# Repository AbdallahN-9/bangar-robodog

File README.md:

# Bangar Robodog (بنجر) 🐕⚙️

### An Assistive Wheeled-Quadruped Robot Dog: Custom Embedded Hardware, ROS 2 & Gazebo Simulation

**Bangar** is an award-winning, custom-engineered **wheeled-quadruped robot dog** developed as an assistive, domestic companion robot. Designed to alleviate elderly loneliness and offer non-intrusive health/emergency monitoring, Bangar integrates custom embedded electronics, 12-DoF hybrid locomotion, and high-fidelity physics simulation in ROS 2 and Gazebo Sim.

---

## 👥 The Team & IEEE Recognition

Project Bangar was engineered by:

* **Abdallah Nabil** — *Electrical System & Gazebo Simulation*
* **Omar Khaled** — *Mechanical Design & Control Software*
* **Omar Barakat** — *Mechanical Assembly & Computer Vision*
* **Khaled Aboelmaety** — *Sensor Integration & System Debugging*

| IEEE ICMISI 2026 Exhibition & Award | IEEE Certificate of Recognition |
| :---: | :---: |
|  |  |
| The team showcasing Bangar at the 2026 IEEE 3rd International Conference on Machine Intelligence and Smart Innovation (ICMISI 2026). | **Official Recognition**: Presented by IEEE and the Arab Academy for Science, Technology & Maritime Transport (AASTMT). |

<p align="center">
  
  <br />
  <em>Concept: Bangar as an assistive companion in home living environments.</em>
</p>

---

## 🛠️ Custom Hardware, PCB & Wiring Integration

Bangar is powered by a custom-designed, multi-layer motherboard developed in **KiCad** ($107.25\text{ mm} \times 92.0\text{ mm}$) to handle power regulation, high-torque servo actuation, and distributed sensor processing:

| Fabricated Motherboard | KiCad 3D Component Layout |
| :---: | :---: |
|  |  |
| **Physical PCB:** Dual microcontroller sockets, screw power rails, blade fuse, and JST headers. | **3D CAD Layout:** Component placement, PCA9685 PWM headers, and terminal connectors. |

| Workbench Wiring & Sensor Testing | Full In-Chassis Electrical Integration |
| :---: | :---: |
|  |  |
| **Bench Testing:** Full testbench wiring with ultrasonic sensor arrays and dual Nano logic. | **Chassis Integration:** LiPo battery pack, buck converters, motherboard, and servo cabling. |

### Motherboard Architecture & Electronics Specifications

* **Processing & Logic:** Dual **Arduino Nano v3.x** microcontrollers for distributed motor control, kinematics timing, and sensor telemetry.
* **Actuator Control:** Dedicated 16-channel **PCA9685** 12-bit PWM servo controller interface (`PCA_In`) driving the 8 shoulder and knee servo motors (`J1`–`J8`, `J18`–`J21`).
* **Multi-Rail Power System:**
  * **12V High-Power Input/Output:** Screw terminal distribution for wheel drive motors and main battery input.
  * **6V High-Current Rail:** Dedicated high-amperage power distribution specifically tuned for the 8 high-torque leg servos.
  * **5V Logic Rail:** Regulated supply for microcontrollers, sensors, and logic lines.
  * **Circuit Protection:** Built-in automotive blade fuse holder and heavy-duty primary power toggle switch.
* **Sensors & Expansion Interfaces:**
  * Multi-channel **Ultrasonic Range Sensors** (`UltraS1`, `UltraS2`, etc.) via polarized JST connectors.
  * **Hall-Effect Wheel Encoders** (`Hall_Effect2`, `Hall_Effect3`) for wheel odometry and speed feedback.
  * **I2C Telemetry Bus:** Exposed SDA, SCL, 5V, GND, and INT breakout for IMU and expansion peripherals.
* **Fabrication Files:** Complete Gerber archives (`hardware/gerber/bangar_107.25x92.0mm_gerber.zip`) ready for direct manufacturing (JLCPCB, PCBWay, etc.).

---

## 📸 Simulation & Kinematics Showcase

| Gazebo Sim Warehouse Environment | RViz2 Kinematics & TF Model |
| :---: | :---: |
|  |  |
| **Gazebo Sim:** ODE physics, custom friction zones ($\mu=0.2$ to $\mu=50$), and navigation arenas. | **RViz2:** Joint coordinate frames, link geometry, acrylic chassis, and top phone mount. |

<p align="center">
  
  <br />
  <em>CAD render showcasing mechanical leg linkages, wheel assemblies, chassis cutouts, and smartphone mount.</em>
</p>

---

## 🌟 Key Locomotion & Software Features

- **Hybrid Legged-Wheeled Locomotion:**
  - **Quadruped Trot Gait:** Diagonal pair trotting (FL+BR in phase, FR+BL in antiphase) with coordinated shoulder sweeps and knee clearance arches.
  - **Differential Wheeled Drive:** 4 powered wheels (Pololu 60×8mm) located at the feet enable zero-radius in-place turns and fast flat-ground translation.
  - **Smooth Eased Poses:** Sitting, standing, and stopping postures generated via cosine easing interpolation.
- **Gazebo Sim Physics & Controllers:**
  - 8 Position PID controllers for shoulders ($P=150$) and knees ($P=40$).
  - 4 Velocity controllers for wheel driving ($P=10.0$).
  - Custom `warehouse_world.sdf` featuring a $30\text{m} \times 24\text{m}$ warehouse arena with colored navigation goals and a low-friction terrain zone ($\mu=0.2$) for traction testing.
- **Perception & Localization:**
  - Smartphone head bracket (`mobile_link`) with DroidCam IP stream integration.
  - Real-time ArUco fiducial marker tracking (`cv2.aruco`) for 2D world pose estimation.
  - ROS 2 message bridging for multi-directional ultrasonic proximity scanning.

---

## 📐 Kinematics & Joint Mapping

Bangar possesses **12 actuated Degrees of Freedom (DoF)**:

| Joint Group | Joints | Type | Limits / Range | Function |
| :--- | :--- | :--- | :--- | :--- |
| **Shoulders (4×)** | `front_left_shoulder_joint`<br>`front_right_shoulder_joint`<br>`back_left_shoulder_joint`<br>`back_right_shoulder_joint` | Revolute | $\pm 0.8\text{ rad}$ ($50\text{ N}\cdot\text{m}$) | Forward/rearward leg swing |
| **Knees (4×)** | `front_left_knee_joint`<br>`front_right_knee_joint`<br>`back_left_knee_joint`<br>`back_right_knee_joint` | Revolute | $\pm 1.2\text{ rad}$ / $\pm 1.4\text{ rad}$ | Leg lifting & ground clearance |
| **Wheels (4×)** | `front_left_wheel_joint`<br>`front_right_wheel_joint`<br>`back_left_wheel_joint`<br>`back_right_wheel_joint` | Continuous | Continuous ($10\text{ rad/s}$) | Driving & skid-steer turning |

---

## 📂 Repository Structure

```
bangar/
├── CMakeLists.txt              # Package build definitions & install targets
├── package.xml                 # ROS 2 package metadata and dependencies
├── README.md                   # Comprehensive project documentation
├── .gitignore                  # Git exclusions for build & temporary files
├── hardware/                   # Custom embedded electronics design
│   ├── kicad/                  # KiCad PCB project, schematic & layout files
│   └── gerber/                 # Ready-to-order manufacturing Gerber packages
├── docs/
│   └── images/                 # Simulation screenshots, PCB photos, wiring & CAD renders
├── config/
│   └── joint_names_Bangar.yaml # Joint names configuration
├── launch/
│   ├── gazebo_launch.py        # Complete headless/macOS-safe Gazebo launch
│   ├── gazebo_walk.launch.py   # Gazebo simulation with walk controller
│   ├── display.launch.py       # Basic robot state display in RViz
│   └── rviz.launch.py          # Interactive RViz2 visualization
├── urdf/
│   ├── bangar.urdf             # Baseline URDF model
│   ├── bangar_gazebo.urdf      # Gazebo simulation model with plugins & PIDs
│   └── bangar.csv              # Link masses, origins, and inertias
├── worlds/
│   └── warehouse_world.sdf     # Custom warehouse simulation arena
├── meshes/                     # STL geometry files for robot links & wheels
└── bangar/                     # ROS 2 Python nodes
    ├── __init__.py
    ├── bangar_controller.py    # Master state machine controller
    ├── walk_node.py            # Diagonal trot gait generator
    ├── wheel_node.py           # Wheel velocity publisher
    ├── sit_node.py             # Cosine-interpolated sitting motion
    ├── turn_left_node.py       # Differential skid turn (left)
    ├── turn_right_node.py      # Differential skid turn (right)
    └── camera_node.py          # ArUco marker pose estimator via camera feed
```

---

## 🚀 Getting Started

### 1. Prerequisites

- **OS:** Linux (Ubuntu 22.04 / 24.04) or macOS (Apple Silicon / Intel via Conda/RoboStack)
- **ROS 2:** Jazzy Jalisco or Humble Hawksbill
- **Gazebo Sim:** Gazebo Harmonic or Fortress (`gz-sim8`)
- **ROS-Gazebo Bridge:** `ros_gz_bridge`, `ros_gz_sim`
- **KiCad (Optional):** KiCad v7 or v8 (to view/edit PCB schematics)
- **Python Dependencies:** `opencv-python`, `numpy`, `cv_bridge`

### 2. Workspace Setup & Build

Clone into your ROS 2 workspace's `src` folder:

```bash
# Create and navigate to your ROS 2 workspace
mkdir -p ~/ros2_ws/src
cd ~/ros2_ws/src

# Clone the repository
git clone https://github.com/AbdallahN-9/bangar-robodog.git bangar

# Install ROS dependencies
cd ~/ros2_ws
rosdep install --from-paths src --ignore-src -r -y

# Build with colcon
colcon build --symlink-install

# Source the overlay
source install/setup.bash
```

*(On macOS using zsh, use `source install/setup.zsh`)*

---

## 🕹️ Running the Simulation

### Option A: Launch Full Gazebo Simulation

To launch the physics server, robot spawn, topic bridges, and behavioral controller:

```bash
ros2 launch bangar gazebo_launch.py
```

*Note for macOS users:* Gazebo server runs headless (`-s`) by default for optimal performance and stability.

### Option B: Interactive State & Motion Control

Command Bangar's locomotion modes on the `/bangar/mode` topic:

```bash
# Start walking (diagonal trot gait + wheel drive)
ros2 topic pub --once /bangar/mode std_msgs/msg/String "{data: 'walk'}"

# Turn left in place (differential wheel drive)
ros2 topic pub --once /bangar/mode std_msgs/msg/String "{data: 'turn_left'}"

# Turn right in place (differential wheel drive)
ros2 topic pub --once /bangar/mode std_msgs/msg/String "{data: 'turn_right'}"

# Sit down smoothly (cosine-interpolated rear leg fold)
ros2 topic pub --once /bangar/mode std_msgs/msg/String "{data: 'sit'}"

# Stand / Stop
ros2 topic pub --once /bangar/mode std_msgs/msg/String "{data: 'stop'}"
```

### Option C: View Kinematics in RViz2

To inspect the robot's URDF model and test gait movements visually without physics:

```bash
ros2 launch bangar rviz.launch.py
```

### Option D: Vision & Marker Tracking

To test ArUco marker pose localization from an IP phone camera feed:

```bash
ros2 run bangar camera_node.py
```

---

## 📡 Key Topics & Bridges

| Topic | Type | Source | Purpose |
| :--- | :--- | :--- | :--- |
| `/joint_states` | `sensor_msgs/msg/JointState` | Gazebo Sim | Current angles & velocities of all 12 joints |
| `/bangar/mode` | `std_msgs/msg/String` | User / Teleop | Mode selector (`walk`, `turn_left`, `sit`, `stop`) |
| `/cmd/*_shoulder` | `std_msgs/msg/Float64` | `bangar_controller` | Commanded shoulder joint target angle (rad) |
| `/cmd/*_knee` | `std_msgs/msg/Float64` | `bangar_controller` | Commanded knee joint target angle (rad) |
| `/cmd/*_wheel` | `std_msgs/msg/Float64` | `bangar_controller` | Commanded wheel joint angular velocity |
| `/bangar/pose_estimate` | `geometry_msgs/msg/PoseWithCovarianceStamped` | `camera_node` | Visual pose estimated from ArUco markers |

---

## 📄 License

This project is licensed under the [BSD-3-Clause License](LICENSE).

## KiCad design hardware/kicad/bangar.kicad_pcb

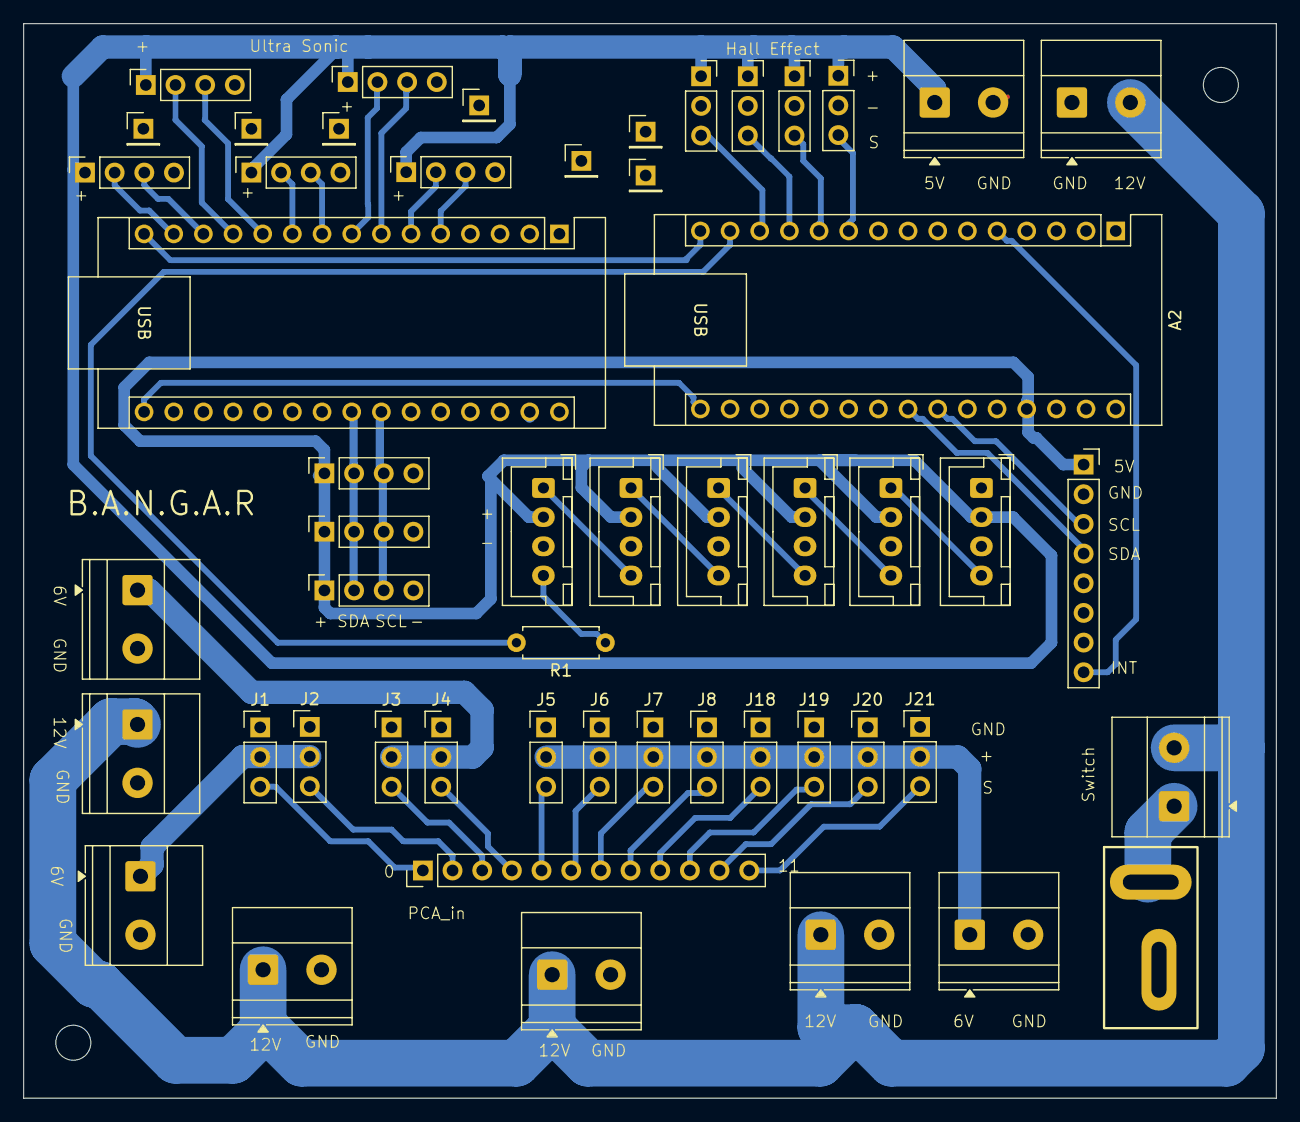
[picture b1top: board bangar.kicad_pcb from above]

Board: 2 copper layers, 107.2 x 92.0 mm, 53 parts (0 on the bottom side), 45 nets.

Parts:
A1, A2: Arduino_Nano_v3.x; Arduino_Nano
J1: Serv0; PinHeader_1x03_P2.54mm_Vertical
J2: Serv1; PinHeader_1x03_P2.54mm_Vertical
J3: Serv2; PinHeader_1x03_P2.54mm_Vertical
J4: Serv3; PinHeader_1x03_P2.54mm_Vertical
J5: Serv4; PinHeader_1x03_P2.54mm_Vertical
J6: Serv5; PinHeader_1x03_P2.54mm_Vertical
J7: Serv6; PinHeader_1x03_P2.54mm_Vertical
J8: Serv7; PinHeader_1x03_P2.54mm_Vertical
J9: UltraS1; PinSocket_1x04_P2.54mm_Vertical
J10: UltraS2; PinSocket_1x04_P2.54mm_Vertical
J11: UltraS3; PinSocket_1x04_P2.54mm_Vertical
J12: UltraS4; PinSocket_1x04_P2.54mm_Vertical
J14: 6V_Buck_2; TerminalBlock_Phoenix_MKDS-1,5-2_1x02_P5.00mm_Horizontal
J15: 6V_Buck_3; TerminalBlock_Phoenix_MKDS-1,5-2_1x02_P5.00mm_Horizontal
J16: 6V_Buck_4; TerminalBlock_Phoenix_MKDS-1,5-2_1x02_P5.00mm_Horizontal
J17: 5V_Buck; TerminalBlock_Phoenix_MKDS-1,5-2_1x02_P5.00mm_Horizontal
J18: Serv8; PinHeader_1x03_P2.54mm_Vertical
J19: Serv9; PinHeader_1x03_P2.54mm_Vertical
J20: Serv10; PinHeader_1x03_P2.54mm_Vertical
J21: Serv11; PinHeader_1x03_P2.54mm_Vertical
J22: PCA9685_in; PinHeader_1x12_P2.54mm_Vertical
J23: PCA; PinSocket_1x04_P2.54mm_Vertical
J24: Heart sensor; PinSocket_1x04_P2.54mm_Vertical
J25: mpu6050; PinSocket_1x08_P2.54mm_Vertical
J26: UltraS5; PinSocket_1x04_P2.54mm_Vertical
J27: Extra; PinSocket_1x04_P2.54mm_Vertical
J28: Hall_Effect1; PinSocket_1x03_P2.54mm_Vertical
J29: Hall_Effect2; PinSocket_1x03_P2.54mm_Vertical
J30: Hall_Effect3; PinSocket_1x03_P2.54mm_Vertical
J31: Hall_Effect4; PinSocket_1x03_P2.54mm_Vertical
J32: LED2; JST_XH_B4B-XH-A_1x04_P2.50mm_Vertical
J33: LED3; JST_XH_B4B-XH-A_1x04_P2.50mm_Vertical
J34: LED4; JST_XH_B4B-XH-A_1x04_P2.50mm_Vertical
J35: LED5; JST_XH_B4B-XH-A_1x04_P2.50mm_Vertical
J36: LED6; JST_XH_B4B-XH-A_1x04_P2.50mm_Vertical
J37: Dean_T_connector
J38: LED1; JST_XH_B4B-XH-A_1x04_P2.50mm_Vertical
J39, J39#2, J40, J41, J42: 12v out; TerminalBlock_Phoenix_MKDS-1,5-2_1x02_P5.00mm_Horizontal
J43: Switch; TerminalBlock_Phoenix_MKDS-1,5-2_1x02_P5.00mm_Horizontal
J44, J45, J46, J47, J48, J49, J49#2: Conn_01x01_Pin; PinHeader_1x01_P2.54mm_Vertical
R1: R; R_Axial_DIN0207_L6.3mm_D2.5mm_P7.62mm_Horizontal

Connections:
5V: A2.27 (+5V), J9.1, J10.1, J11.1, J12.1, J17.1, J23.1, J24.1, J25.1, J26.1, J27.1, J28.1, J29.1, J30.1, J31.1, J32.2, J33.2, J34.2, J35.2, J36.2, J38.2
6V: J1.2, J2.2, J3.2, J4.2, J5.2, J6.2, J7.2, J8.2, J14.1, J15.1, J16.1, J18.2, J19.2, J20.2, J21.2
12: J39.2, J39#2.1, J40.1, J41.1, J42.1, J43.2
Battery_out: J37.1 (+), J43.1
D2: A1.5 (D2), J9.3
D3: A1.6 (D3), J9.2
D4: A1.7 (D4), J10.3
D5: A1.8 (D5), J10.2
D6: A1.9 (D6), J11.3
D7: A1.10 (D7), J11.2
D8: A1.11 (D8), J12.3
D9: A1.12 (D9), J12.2
D10: A1.13 (D10), J26.3
D11: A1.14 (D11), J26.2
D12: A1.15 (D12), A2.15 (D12)
D13: A1.16 (D13), A2.16 (D13)
GND: A1.4 (GND), A1.29 (GND), A2.4 (GND), A2.29 (GND), J1.1, J2.1, J3.1, J4.1, J5.1, J6.1, J7.1, J8.1, J9.4, J10.4, J11.4, J12.4, J14.2, J15.2, J16.2, J17.2, J18.1, J19.1, J20.1, J21.1, J23.4, J24.4, J25.2, J26.4, J27.4, J28.2, J29.2, J30.2, J31.2, J32.3, J33.3, J34.3, J35.3, J36.3, J37.2 (_), J38.3, J39.1, J39#2.2, J40.2, J41.2, J42.2, J44.1, J45.1, J46.1, J47.1, J48.1, J49.1, J49#2.1
unnamed: A2.23 (A4), J25.4
unnamed: A2.24 (A5), J25.3
unnamed: A2.5 (D2), J25.8
unnamed: A2.10 (D7), J28.3
unnamed: A2.11 (D8), J29.3
unnamed: A2.12 (D9), J30.3
unnamed: A2.13 (D10), J31.3
unnamed: J32.1, J38.4
unnamed: J32.4, J33.1
unnamed: J33.4, J34.1
unnamed: J34.4, J35.1
unnamed: J35.4, J36.1
unnamed: J36.4, R1.1
SCL: A1.24 (A5), J23.3, J24.3, J27.3
SDA: A1.23 (A4), J23.2, J24.2, J27.2
Servo_0: J1.3, J22.1
Servo_1: J2.3, J22.2
Servo_2: J3.3, J22.3
Servo_3: J4.3, J22.4
Servo_4: J5.3, J22.5
Servo_5: J6.3, J22.6
Servo_6: J7.3, J22.7
Servo_7: J8.3, J22.8
Servo_8: J18.3, J22.9
Servo_9: J19.3, J22.10
Servo_10: J20.3, J22.11
Servo_11: J21.3, J22.12
led d11: A2.14 (D11), R1.2

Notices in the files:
README.md:
License: BSD-3-Clause
